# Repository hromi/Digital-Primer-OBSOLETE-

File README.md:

# Digital-Primer
 In this repository You will find some necessary software bricks which will allow You to create Your own variant of a digital Primer (DP). DP is a new kind of medium whose raison d'etre is to educate. Its ideal hardware embodiment looks like a book and has multiple properties of a book. Instead of using screens, device uses e-ink displays (mostly using IT8951 controller) to present visual or textual content. Strong emphasis is to be put on speech technologies (automatic speech recognition and speech synthesis) and touchless human-machine interaction. Recommended platform: Raspberry Pi Zero running Raspbian OS.

#Structure
Fibel has a following structure:

Curriculum -> Epoch -> Lection -> Exercise

Curriculum (e.g. "Lesen") and Epoch (e.g. "Tiere") form a topic with specific TOPIC_DIR (e.g. Lesen/Tiere/)

Folios are associated to topics and lessons mix specific folios associated to the topic.

Folio-mixing is attained by means of symlinks.

How to generate folios for a new topic:
1) specify the font (e.g. 'schola'), voice (e.g. 'ask') and drawing (e.g. 'lux') authors
2) populate the Lexicon with Your BMP images and WAV recordings
3) create the "Units" subdir of the TOPIC_DIR populated with files whose names match names of subdirs in the lexicon
4) run python3 generate_foliae.py TOPIC_DIR 

How to create new lesson:
1) Generate folios for a new topic (c.f. above)
2) Within the topic dir, create the "Lectiones" subdir (e.g. TOPIC_DIR/Lectiones/)
3) Within the Lectiones subdir, create the lesson subdir whose name is identic to numeric LESSON_ID (e.g. TOPIC_DIR/Lectiones/1)
4) Within the "Deck" subdir of a specific lesson subdir, create symlinks to topic Foliae. Symlink names should be sorted according to the sequence in which You want Folios to get loaded (and potentially also appear)
5) run python3 generate_lesson.py TOPIC_DIR LESSON_ID

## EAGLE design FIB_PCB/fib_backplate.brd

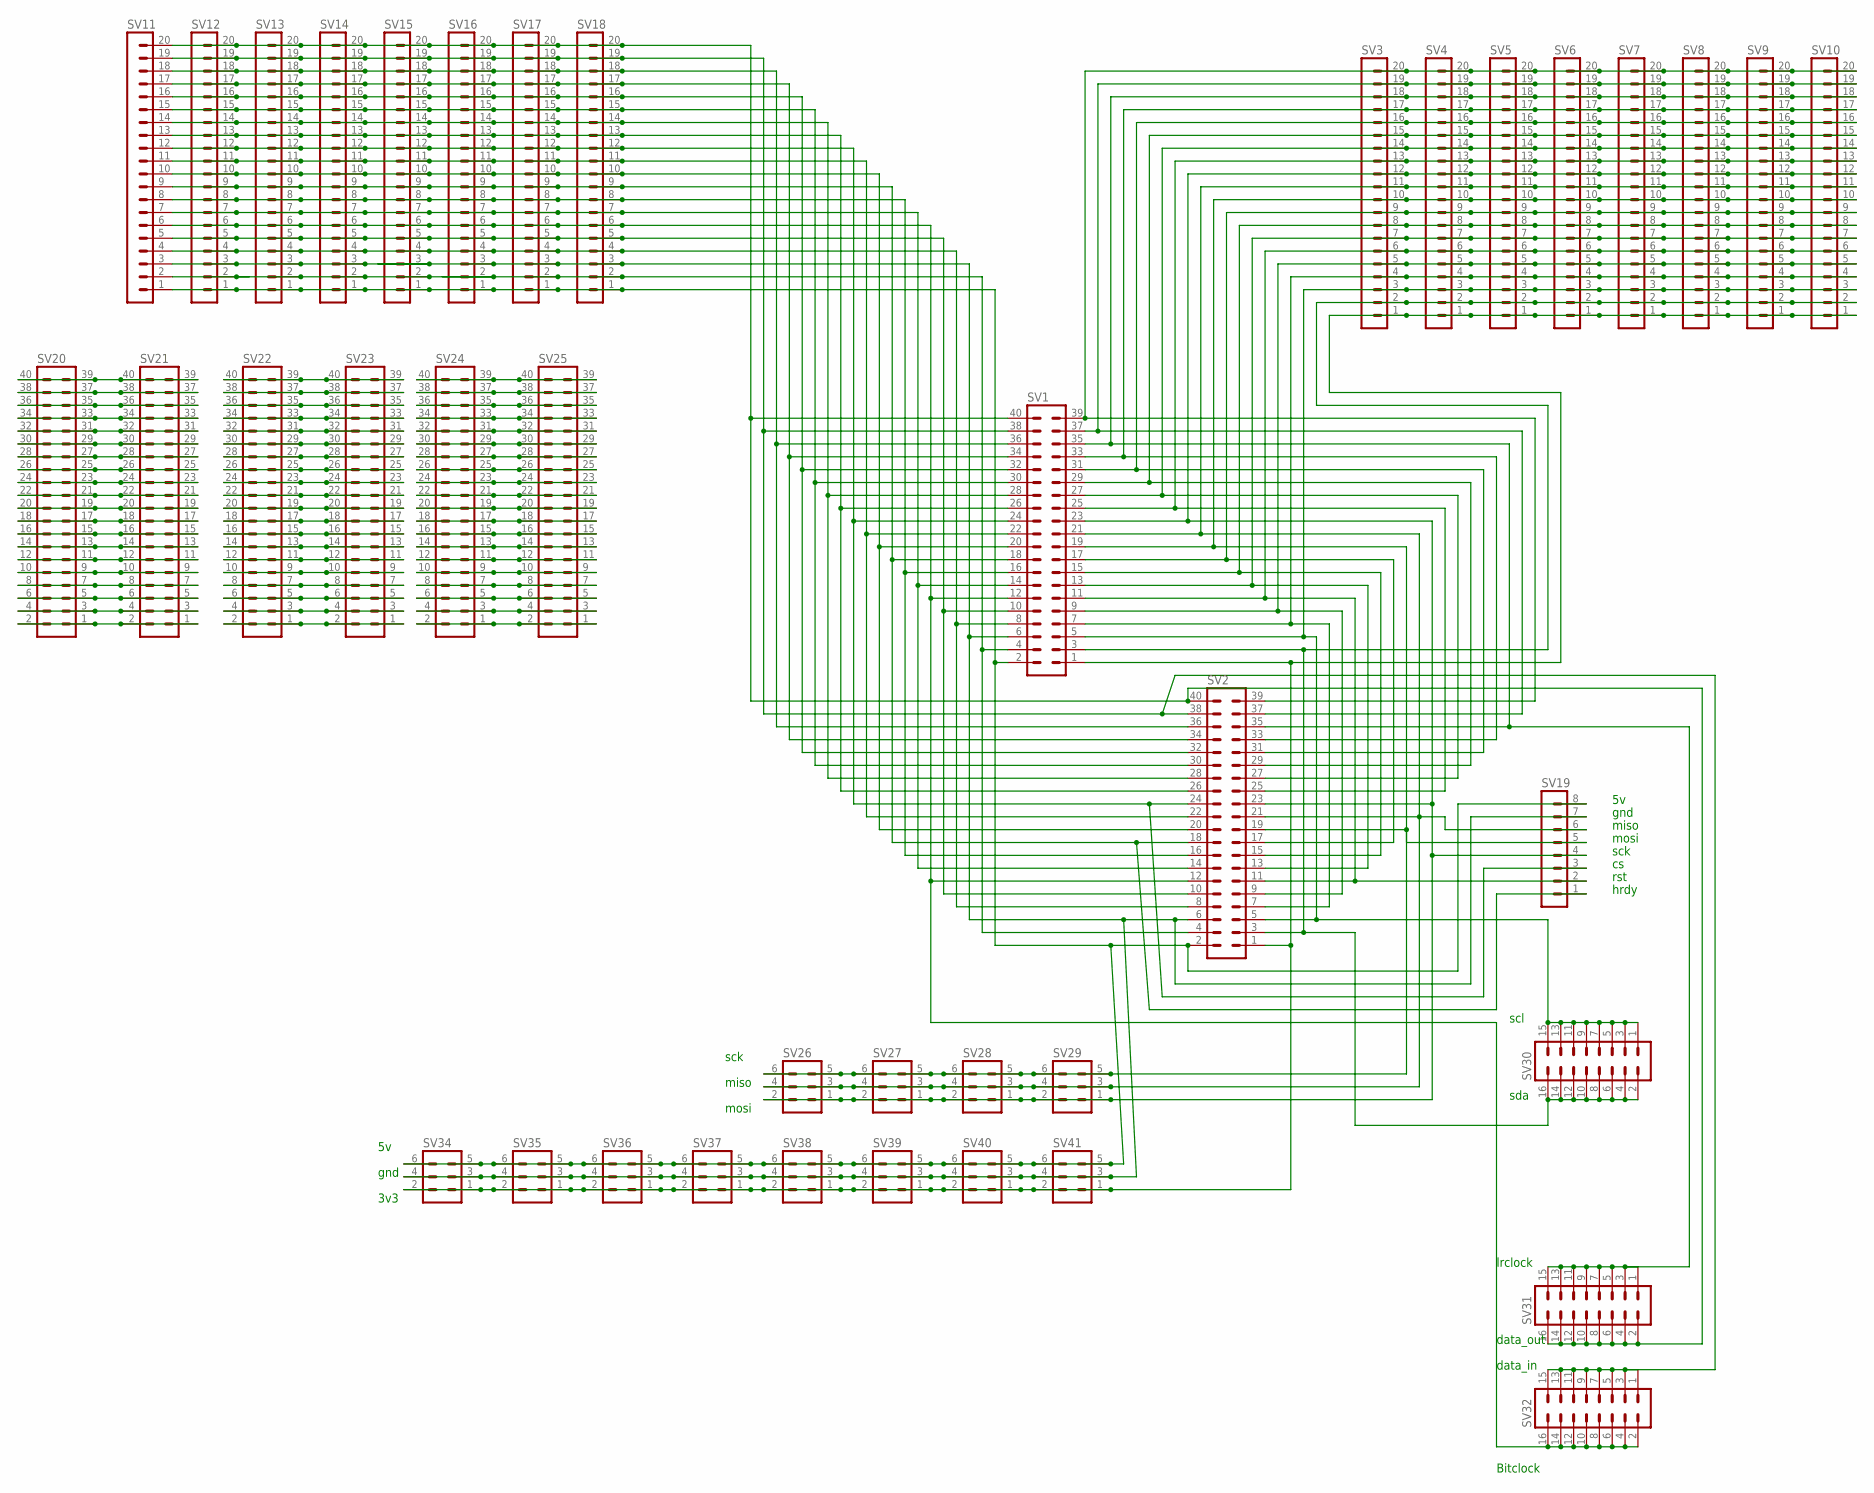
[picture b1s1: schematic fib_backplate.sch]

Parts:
SV1, SV2, SV20, SV21, SV22, SV23, SV24, SV25: MA20-2
SV3, SV4, SV5, SV6, SV7, SV8, SV9, SV10, SV11, SV12, SV13, SV14, SV15, SV16, SV17, SV18: MA20-1L
SV19: MA08-1
SV26, SV27, SV28, SV29, SV34, SV35, SV36, SV37, SV38, SV39, SV40, SV41: MA03-2
SV30, SV31, SV32: MA08-2

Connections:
unnamed: SV1.4, SV2.4, SV11.2, SV12.2, SV13.2, SV14.2, SV15.2, SV16.2, SV17.2, SV18.2
unnamed: SV1.8, SV2.8, SV11.4, SV12.4, SV13.4, SV14.4, SV15.4, SV16.4, SV17.4, SV18.4
unnamed: SV1.10, SV2.10, SV11.5, SV12.5, SV13.5, SV14.5, SV15.5, SV16.5, SV17.5, SV18.5
unnamed: SV1.35, SV2.35, SV3.18, SV4.18, SV5.18, SV6.18, SV7.18, SV8.18, SV9.18, SV10.18, SV31.1, SV31.3, SV31.5, SV31.7, SV31.9, SV31.11, SV31.13, SV31.15
unnamed: SV1.12, SV2.12, SV11.6, SV12.6, SV13.6, SV14.6, SV15.6, SV16.6, SV17.6, SV18.6, SV32.2, SV32.4, SV32.6, SV32.8, SV32.10, SV32.12, SV32.14, SV32.16
unnamed: SV1.14, SV2.14, SV11.7, SV12.7, SV13.7, SV14.7, SV15.7, SV16.7, SV17.7, SV18.7
unnamed: SV1.5, SV2.5, SV3.3, SV4.3, SV5.3, SV6.3, SV7.3, SV8.3, SV9.3, SV10.3, SV30.1, SV30.3, SV30.5, SV30.7, SV30.9, SV30.11, SV30.13, SV30.15
unnamed: SV1.7, SV2.7, SV3.4, SV4.4, SV5.4, SV6.4, SV7.4, SV8.4, SV9.4, SV10.4
unnamed: SV1.9, SV2.9, SV3.5, SV4.5, SV5.5, SV6.5, SV7.5, SV8.5, SV9.5, SV10.5
unnamed: SV20.39, SV20.40, SV21.39, SV21.40
unnamed: SV1.11, SV2.11, SV3.6, SV4.6, SV5.6, SV6.6, SV7.6, SV8.6, SV9.6, SV10.6, SV19.2
unnamed: SV1.18, SV2.18, SV11.9, SV12.9, SV13.9, SV14.9, SV15.9, SV16.9, SV17.9, SV18.9, SV19.1
unnamed: SV20.37, SV20.38, SV21.37, SV21.38
unnamed: SV1.13, SV2.13, SV3.7, SV4.7, SV5.7, SV6.7, SV7.7, SV8.7, SV9.7, SV10.7
unnamed: SV1.22, SV2.22, SV11.11, SV12.11, SV13.11, SV14.11, SV15.11, SV16.11, SV17.11, SV18.11
unnamed: SV1.15, SV2.15, SV3.8, SV4.8, SV5.8, SV6.8, SV7.8, SV8.8, SV9.8, SV10.8
unnamed: SV20.35, SV20.36, SV21.35, SV21.36
unnamed: SV1.17, SV2.17, SV3.9, SV4.9, SV5.9, SV6.9, SV7.9, SV8.9, SV9.9, SV10.9
unnamed: SV20.33, SV20.34, SV21.33, SV21.34
unnamed: SV1.25, SV2.25, SV3.13, SV4.13, SV5.13, SV6.13, SV7.13, SV8.13, SV9.13, SV10.13
unnamed: SV20.31, SV20.32, SV21.31, SV21.32
unnamed: SV20.29, SV20.30, SV21.29, SV21.30
unnamed: SV20.27, SV20.28, SV21.27, SV21.28
unnamed: SV1.27, SV2.27, SV3.14, SV4.14, SV5.14, SV6.14, SV7.14, SV8.14, SV9.14, SV10.14
unnamed: SV20.25, SV20.26, SV21.25, SV21.26
unnamed: SV1.29, SV2.29, SV3.15, SV4.15, SV5.15, SV6.15, SV7.15, SV8.15, SV9.15, SV10.15
unnamed: SV1.31, SV2.31, SV3.16, SV4.16, SV5.16, SV6.16, SV7.16, SV8.16, SV9.16, SV10.16
unnamed: SV20.23, SV20.24, SV21.23, SV21.24
unnamed: SV20.21, SV20.22, SV21.21, SV21.22
unnamed: SV1.28, SV2.28, SV11.14, SV12.14, SV13.14, SV14.14, SV15.14, SV16.14, SV17.14, SV18.14
unnamed: SV1.33, SV2.33, SV3.17, SV4.17, SV5.17, SV6.17, SV7.17, SV8.17, SV9.17, SV10.17
unnamed: SV1.32, SV2.32, SV11.16, SV12.16, SV13.16, SV14.16, SV15.16, SV16.16, SV17.16, SV18.16
unnamed: SV1.36, SV2.36, SV11.18, SV12.18, SV13.18, SV14.18, SV15.18, SV16.18, SV17.18, SV18.18
unnamed: SV1.37, SV2.37, SV3.19, SV4.19, SV5.19, SV6.19, SV7.19, SV8.19, SV9.19, SV10.19
unnamed: SV20.19, SV20.20, SV21.19, SV21.20
unnamed: SV1.26, SV2.26, SV11.13, SV12.13, SV13.13, SV14.13, SV15.13, SV16.13, SV17.13, SV18.13
unnamed: SV20.17, SV20.18, SV21.17, SV21.18
unnamed: SV1.30, SV2.30, SV11.15, SV12.15, SV13.15, SV14.15, SV15.15, SV16.15, SV17.15, SV18.15
unnamed: SV20.15, SV20.16, SV21.15, SV21.16
unnamed: SV1.34, SV2.34, SV11.17, SV12.17, SV13.17, SV14.17, SV15.17, SV16.17, SV17.17, SV18.17
unnamed: SV20.13, SV20.14, SV21.13, SV21.14
unnamed: SV1.38, SV2.38, SV11.19, SV12.19, SV13.19, SV14.19, SV15.19, SV16.19, SV17.19, SV18.19, SV32.1, SV32.3, SV32.5, SV32.7, SV32.9, SV32.11, SV32.13, SV32.15
unnamed: SV1.40, SV2.40, SV11.20, SV12.20, SV13.20, SV14.20, SV15.20, SV16.20, SV17.20, SV18.20, SV31.2, SV31.4, SV31.6, SV31.8, SV31.10, SV31.12, SV31.14, SV31.16
unnamed: SV20.11, SV20.12, SV21.11, SV21.12
unnamed: SV20.9, SV20.10, SV21.9, SV21.10
unnamed: SV20.7, SV20.8, SV21.7, SV21.8
unnamed: SV20.5, SV20.6, SV21.5, SV21.6
unnamed: SV20.3, SV20.4, SV21.3, SV21.4
unnamed: SV20.1, SV20.2, SV21.1, SV21.2
unnamed: SV22.39, SV22.40, SV23.39, SV23.40
unnamed: SV22.37, SV22.38, SV23.37, SV23.38
unnamed: SV22.35, SV22.36, SV23.35, SV23.36
unnamed: SV22.33, SV22.34, SV23.33, SV23.34
unnamed: SV22.31, SV22.32, SV23.31, SV23.32
unnamed: SV22.29, SV22.30, SV23.29, SV23.30
unnamed: SV22.27, SV22.28, SV23.27, SV23.28
unnamed: SV22.25, SV22.26, SV23.25, SV23.26
unnamed: SV22.23, SV22.24, SV23.23, SV23.24
unnamed: SV22.21, SV22.22, SV23.21, SV23.22
unnamed: SV22.19, SV22.20, SV23.19, SV23.20
unnamed: SV22.17, SV22.18, SV23.17, SV23.18
unnamed: SV22.15, SV22.16, SV23.15, SV23.16
unnamed: SV22.13, SV22.14, SV23.13, SV23.14
unnamed: SV22.11, SV22.12, SV23.11, SV23.12
unnamed: SV22.9, SV22.10, SV23.9, SV23.10
unnamed: SV22.7, SV22.8, SV23.7, SV23.8
unnamed: SV22.5, SV22.6, SV23.5, SV23.6
unnamed: SV22.3, SV22.4, SV23.3, SV23.4
unnamed: SV22.1, SV22.2, SV23.1, SV23.2
unnamed: SV24.39, SV24.40, SV25.39, SV25.40
unnamed: SV24.37, SV24.38, SV25.37, SV25.38
unnamed: SV24.35, SV24.36, SV25.35, SV25.36
unnamed: SV24.33, SV24.34, SV25.33, SV25.34
unnamed: SV24.31, SV24.32, SV25.31, SV25.32
unnamed: SV24.29, SV24.30, SV25.29, SV25.30
unnamed: SV24.27, SV24.28, SV25.27, SV25.28
unnamed: SV24.25, SV24.26, SV25.25, SV25.26
unnamed: SV24.23, SV24.24, SV25.23, SV25.24
unnamed: SV24.21, SV24.22, SV25.21, SV25.22
unnamed: SV24.19, SV24.20, SV25.19, SV25.20
unnamed: SV24.17, SV24.18, SV25.17, SV25.18
unnamed: SV24.15, SV24.16, SV25.15, SV25.16
unnamed: SV24.13, SV24.14, SV25.13, SV25.14
unnamed: SV24.11, SV24.12, SV25.11, SV25.12
unnamed: SV24.9, SV24.10, SV25.9, SV25.10
unnamed: SV24.7, SV24.8, SV25.7, SV25.8
unnamed: SV24.5, SV24.6, SV25.5, SV25.6
unnamed: SV24.3, SV24.4, SV25.3, SV25.4
unnamed: SV24.1, SV24.2, SV25.1, SV25.2
unnamed: SV1.19, SV2.19, SV3.10, SV4.10, SV5.10, SV6.10, SV7.10, SV8.10, SV9.10, SV10.10, SV19.5, SV26.5, SV26.6, SV27.5, SV27.6, SV28.5, SV28.6, SV29.5, SV29.6
unnamed: SV1.21, SV2.21, SV3.11, SV4.11, SV5.11, SV6.11, SV7.11, SV8.11, SV9.11, SV10.11, SV19.6, SV26.3, SV26.4, SV27.3, SV27.4, SV28.3, SV28.4, SV29.3, SV29.4
unnamed: SV1.23, SV2.23, SV3.12, SV4.12, SV5.12, SV6.12, SV7.12, SV8.12, SV9.12, SV10.12, SV19.4, SV26.1, SV26.2, SV27.1, SV27.2, SV28.1, SV28.2, SV29.1, SV29.2
unnamed: SV1.2, SV2.2, SV11.1, SV12.1, SV13.1, SV14.1, SV15.1, SV16.1, SV17.1, SV18.1, SV19.8, SV34.5, SV34.6, SV35.5, SV35.6, SV36.5, SV36.6, SV37.5, SV37.6, SV38.5, SV38.6, SV39.5, SV39.6, SV40.5, SV40.6, SV41.5, SV41.6
unnamed: SV1.6, SV2.6, SV11.3, SV12.3, SV13.3, SV14.3, SV15.3, SV16.3, SV17.3, SV18.3, SV19.7, SV34.3, SV34.4, SV35.3, SV35.4, SV36.3, SV36.4, SV37.3, SV37.4, SV38.3, SV38.4, SV39.3, SV39.4, SV40.3, SV40.4, SV41.3, SV41.4
unnamed: SV1.1, SV2.1, SV3.1, SV4.1, SV5.1, SV6.1, SV7.1, SV8.1, SV9.1, SV10.1, SV34.1, SV34.2, SV35.1, SV35.2, SV36.1, SV36.2, SV37.1, SV37.2, SV38.1, SV38.2, SV39.1, SV39.2, SV40.1, SV40.2, SV41.1, SV41.2
unnamed: SV1.3, SV2.3, SV3.2, SV4.2, SV5.2, SV6.2, SV7.2, SV8.2, SV9.2, SV10.2, SV30.2, SV30.4, SV30.6, SV30.8, SV30.10, SV30.12, SV30.14, SV30.16
unnamed: SV1.39, SV2.39, SV3.20, SV4.20, SV5.20, SV6.20, SV7.20, SV8.20, SV9.20, SV10.20
unnamed: SV1.16, SV2.16, SV11.8, SV12.8, SV13.8, SV14.8, SV15.8, SV16.8, SV17.8, SV18.8
unnamed: SV1.24, SV2.24, SV11.12, SV12.12, SV13.12, SV14.12, SV15.12, SV16.12, SV17.12, SV18.12, SV19.3
unnamed: SV1.20, SV2.20, SV11.10, SV12.10, SV13.10, SV14.10, SV15.10, SV16.10, SV17.10, SV18.10

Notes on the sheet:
Bitclock
lrclock
data_in
data_out
sda
scl
gnd
miso
mosi
sck
rst
hrdy
3v3

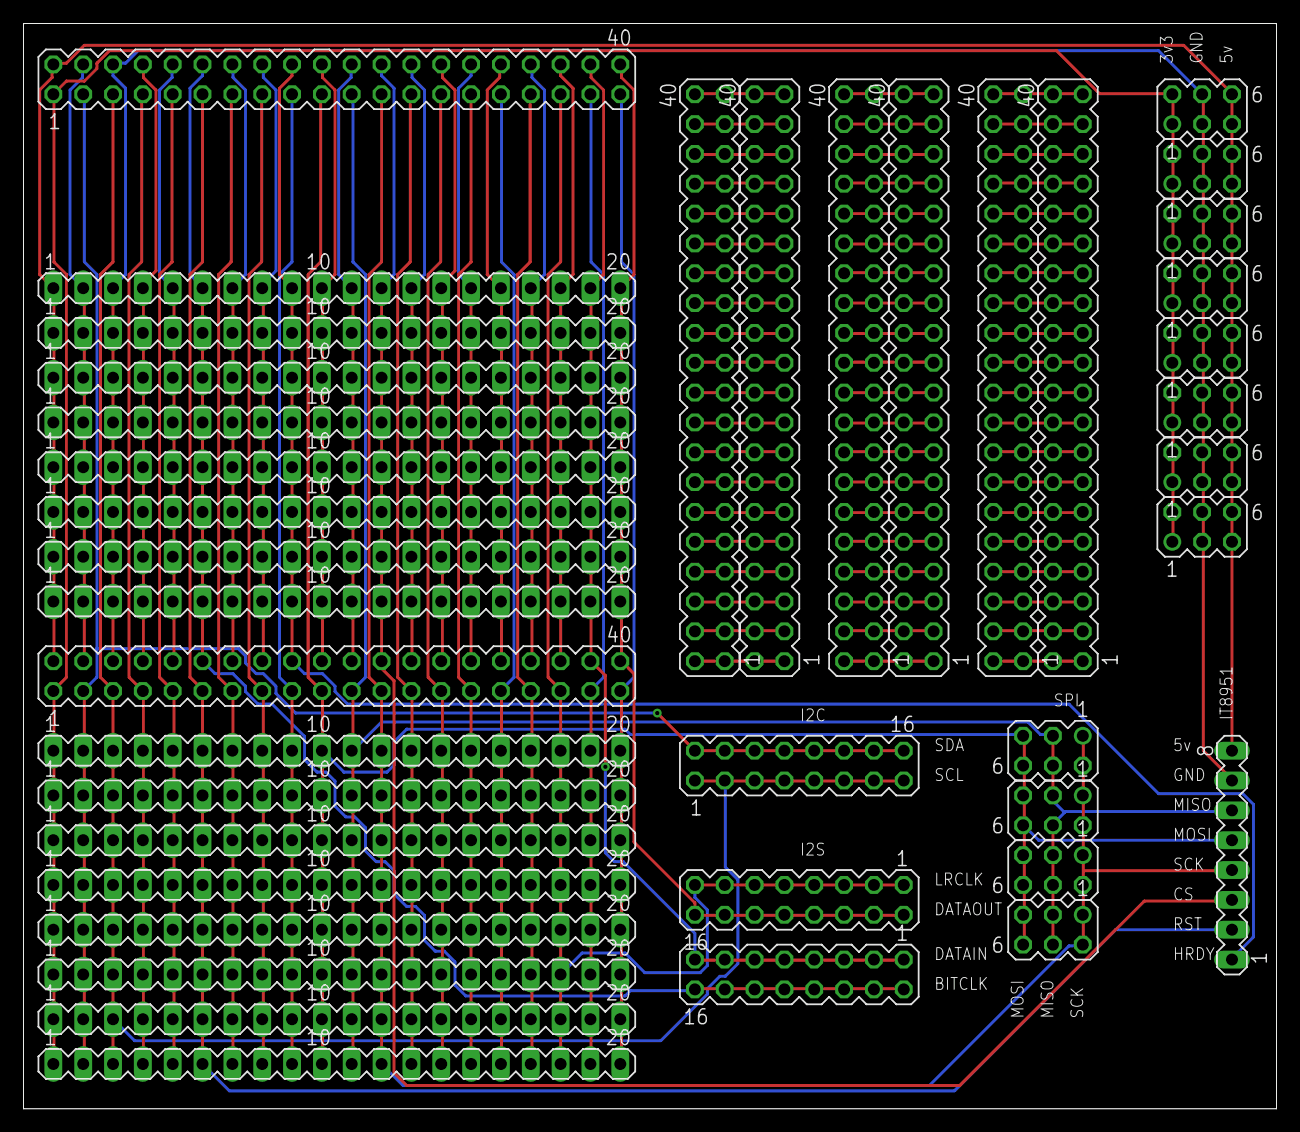
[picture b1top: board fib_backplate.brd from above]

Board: 2 copper layers, 106.7 x 92.4 mm, 40 parts (0 on the bottom side), 100 nets.

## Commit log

2020-03-05 Ave Eris, ave Discordia gratia Plena!
2020-04-06 add pcb files
